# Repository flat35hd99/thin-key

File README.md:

# Thin-key

- Kailh x switch
- 4x1 matrix
- 77 mm x 44 mm
  - You can order this pcb for 2dollars at JLCPCB
- Raspberry Pi Pico

## How to create

[See this build guide page](BUILD_GUIDE.md)

## Pictures

If you create your product, Please make PR with your pictures!

Scheme image

The front side of PCB manufactured by JLCPCB.

The back side of PCB manufactured by JLCPCB.

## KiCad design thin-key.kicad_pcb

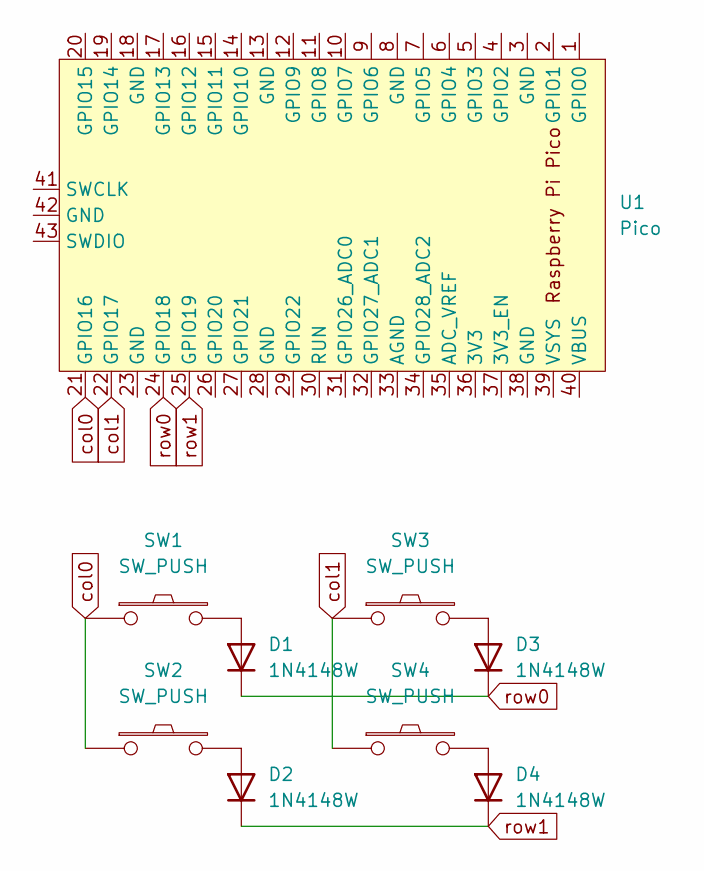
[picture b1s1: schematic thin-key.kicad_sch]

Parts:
D1, D2, D3, D4: 1N4148W; D_SOD-123
SW1, SW2, SW3, SW4: SW_PUSH; Kailh-PG1425-X-Switch
U1: Pico; RPi_Pico_SMD_TH

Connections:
unnamed: D1.2 (A), SW1.2
unnamed: D2.2 (A), SW2.2
unnamed: D3.2 (A), SW3.2
unnamed: D4.2 (A), SW4.2
col0: SW1.1, SW2.1, U1.21 (GPIO16)
col1: SW3.1, SW4.1, U1.22 (GPIO17)
row0: D1.1 (K), D3.1 (K), U1.24 (GPIO18)
row1: D2.1 (K), D4.1 (K), U1.25 (GPIO19)

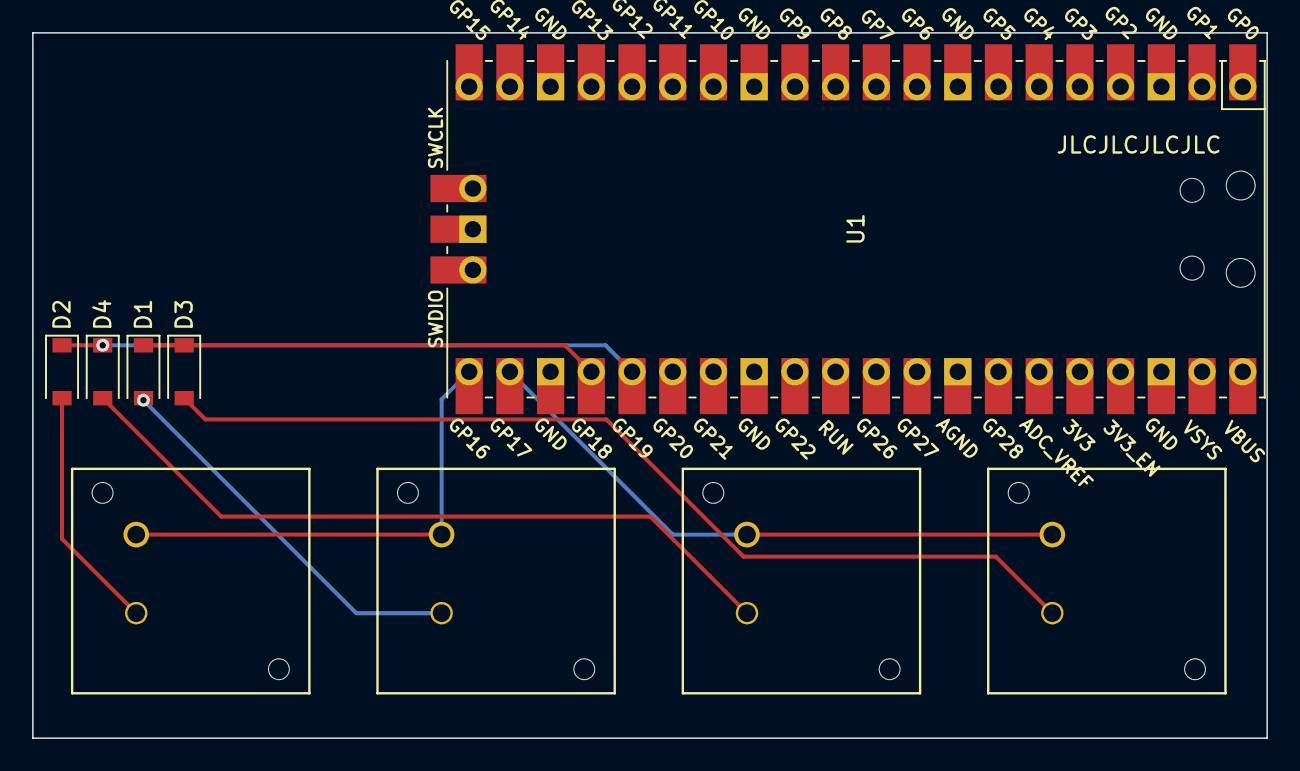
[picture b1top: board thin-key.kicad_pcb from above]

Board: 2 copper layers, 77.0 x 44.0 mm, 9 parts (0 on the bottom side), 8 nets.

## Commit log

2022-07-02 init
2022-07-02 Add libraries
2022-07-02 Add ignore for backup generated by kicad
2022-07-02 Update module
2022-07-02 Finish
2022-07-02 Add jlcjlcjlcjlc
2022-07-02 Add readme
2022-07-02 Add workflow
2022-07-02 Rename kiplot
2022-07-02 Use kibot
2022-07-02 Fix workflow
2022-07-02 Fix output directory
2022-07-02 Create LICENSE
2022-07-04 Use single layer
2022-07-21 Add production pictures
2022-07-21 Add sample keymap
2022-07-21 Add build guide
2022-07-21 Update file name of firmware
2022-07-21 Add via feature to firmware
2022-08-28 Finilize project
2022-08-28 Add buildguide
2022-08-28 Add eye cache
